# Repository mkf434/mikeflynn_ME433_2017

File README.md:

Name: Mike Flynn
Date: September 2017

This repository has my homework files and anything else I needed to create for ME433: Advanced Mechantronics at Northwestern

Here is another line I'm writing to modify the file on my computer locally to make double sure I know how to commit modifed files

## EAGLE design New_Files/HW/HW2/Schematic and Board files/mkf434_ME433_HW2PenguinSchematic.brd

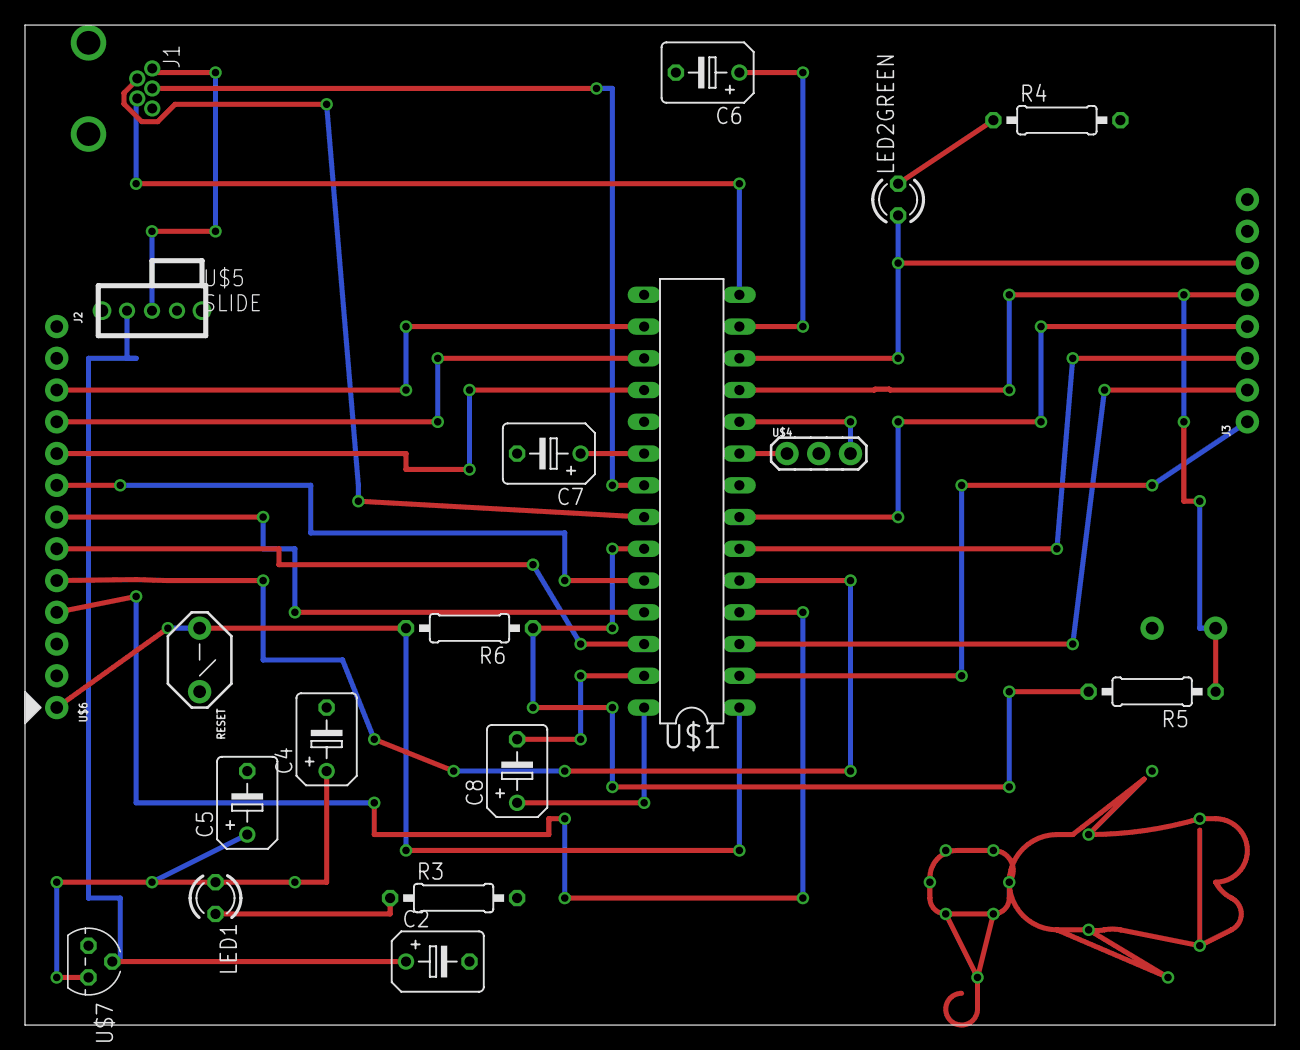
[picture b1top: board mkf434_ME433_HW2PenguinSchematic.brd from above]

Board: 2 copper layers, 100.0 x 80.0 mm, 22 parts (1 on the bottom side), 31 nets.

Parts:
C2, C4, C6, C8: 0.1uF; B45181B
C5, C7: 10uF; B45181B
J1: USB-MB-H
J2, J3: 1X08
LED1, LED2GREEN: LED3MM
R3, R4: 330; 0207/10
R5, R6: 10k; 0207/10
RESET: PB
U$1: PIC32MX250F128B; DIL28-3
U$4: OSC
U$5: SLIDE
U$6: PICKIT3; 1X05
U$7: MCP1702; TO92
USER: PB

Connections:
+3V3: R5.2, R6.1, U$1.23
A0: J3.1, U$1.2
A1: J3.2, U$1.3
A4/LED: J3.6, LED2GREEN.A, U$1.12
B2: J3.3, U$1.6
B3: J3.4, U$1.7
B4/USER: J3.5, R5.1, U$1.11, USER.1
B7: J2.3, U$1.16
B8: J2.4, U$1.17
B9: J2.5, U$1.18
B13: J2.6, U$1.24
B14: J2.7, U$1.25
B15: J2.8, U$1.26
D+: J1.D+, U$1.21
D-: J1.D-, U$1.22
GND: C2.-, C4.-, C5.-, C6.-, C7.-, J1.GND, R3.2, R4.2, RESET.2, U$1.8, U$1.19, U$4.2, U$6.3, U$7.1, USER.2
ID: J1.ID, U$1.14
MCLR: R6.2, RESET.1, U$1.1, U$6.1
unnamed: J1.VBUS, U$5.2.
unnamed: C2.+, U$5.1., U$7.2
unnamed: C4.+, C5.+, LED1.A, U$7.3
unnamed: LED1.K, R3.1
unnamed: LED2GREEN.K, R4.1
unnamed: C6.+, U$1.13
unnamed: C7.+, U$1.20
unnamed: C8.+, U$1.28
unnamed: C8.-, U$1.27
OSC1: U$1.9, U$4.1
OSC2: U$1.10, U$4.3
PGC: U$1.5, U$6.5
PGD: U$1.4, U$6.4

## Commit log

2017-04-03 added readme.md finallygit status
2017-04-03 Forgot to save my file
2017-04-03 Update README.md again
2017-04-05 First Deliverable Photo
2017-04-05 Hw1 Question 6 requested picture
2017-04-07 HW3 ZIP Files
2017-08-24 Second half of homework 1 deliverables
2017-08-24 File Name Updates
2017-09-20 Date Change
2018-04-19 Re-organizing repoallowing for easier identification of New Files
2018-04-27 Cleaned out old files, added new hw files, HW1.2.1 and HW1.2.2
2018-04-27 Deleted more extra files, added Hello World for HW1.7
2018-04-27 Started Hello World file and other asscoiated files
2018-04-27 Saved Hello_World433.c
2018-04-27 Deleted Extra File
2018-04-27 Save File
2018-05-03 Adding hw1 updates
2018-05-03 Random Files from MPlab
2018-05-03 Task1
2018-05-03 HW1 Video
2018-05-03 HW2 fies
2018-05-03 HW3 Files
2018-05-03 Missed HW2 files
2018-05-03 Added some lines I deleted because I thought they were vestigle but I put them back once I realized they were in the template on the wiki
2018-05-07 Start of HW4
2018-05-07 Trying to get rid of an 'Untracked file'
2018-05-07 Added Helper Functions into HW4 main
2018-05-08 Silly Changes
2018-05-08 Saving HW4, got a signal from the MCP4902, trying to manipulate it now
2018-05-08 Stragler File
2018-05-08 Saving HW4
2018-05-08 Almost got SPI, signing off
2018-05-13 Almost done with HW4, finished triangle wave, having casting problems using sin() with doubles butneeding ints for SPI
2018-05-13 Random File
2018-05-13 Homework 4 finished, just need to clean up the code and draw the schematic
2018-05-13 Finished HW4, onto HW5, can't stop wont stop
2018-05-13 Homework 5 is well underway, just put in the I2C functions from github and put in the helper function prototypes mentionedin the instructions
2018-05-13 Added more things, writing init functions and mcp23008 register init functions
2018-05-13 Finished first draft of the code, about to turn it on, potential second first try success ever
2018-05-13 Wrote the main function, seems to easy to be correct
2018-05-13 Had the wrong master_setup values, also had the wrong slave address bits
2018-05-14 Got the MCP23008 to output and have basic right control, now I need to verify that my read is correct
2018-05-14 Finished homework 5, something might be wrong with my GP7, but I got creative with it so we good
2018-05-14 Added video
2018-05-14 Cleaned up the comments on HW5 and added a header comment to HW1
2018-05-14 Stragler Files
2018-05-14 Almost forgot the picture of the circuit
2018-05-14 Rolling right along, created the HW6 folder
2018-05-14 Changed some HW5 stuff, started adding the files needed for the LCD driver
2018-05-14 Changed file and project names to the homework they correspond to and the main files to mainx.c where x is the homework#
2018-05-14 Changed some reference files
2018-05-14 Saving HW6 progress
2018-05-15 Almost finished with the first function
2018-05-15 Finished the writing a character function
2018-05-15 Finished HW6, just adding in the final comments and cleaning everything up etc, signing off for the night
2018-05-15 Finished everything in homework 6
2018-05-15 Created Main file skeleton and started homework 7
2018-05-15 HW7 changes
2018-05-17 Did some directory reorganization, added a LCD and I2C library from past hws
2018-05-17 Hopefully this adds all new files
2018-05-18 Recieved Correct WHO_AM_I response from pololu chip
2018-05-18 Missed some files
2018-05-18 Straglers
2018-05-20 Almost finished with HW7, not sure what the units of the data being sent is, need to ask marchuk
2018-05-20 Adding Stuff
2018-05-20 More
2018-05-21 HW8 done, once I finish off the bugs from HW6 and HW7, HW9 is well underway as well
2018-05-21 Stagler
2018-06-04 Added a lot of stuff
2018-06-04 Wheel
2018-06-04 Hello
2018-06-04 Finished CAD and Laser Files
2018-06-05 Completely finished HW6, resolved issue where chars were writing over each other
2018-06-05 HW6 Video Added
2018-06-05 Finished HW8, just need to finish HW7 accel bars
2018-06-05 Restarted HW9 and almost back to where I was, didn't work the first time so I regenerated the code to make sure I set everything up correctly
2018-06-05 Stragler
2018-06-05 Had to change New Files to New_Files bc of Andriod Developer IDE
2018-06-05 Changed 'Old Files' also for continuity
2018-06-05 Cleaning House
2018-06-05 Still cleaning, hopefully I don't delete everything
2018-06-05 Started Andriod Hello World
2018-06-06 Almost done with Android Hello World App
2018-06-06 Finished HW 12
2018-06-06 Added HW12 Demo Video
2018-06-09 Added Photo of current wiring
2018-06-09 Added first version of living hinge
2018-06-09 Edited HW12 and HW13
2018-06-09 Added HW18 Code
2018-06-09 Added V2 Wheels with correctly fitting o rings
2018-06-10 Started Final PCB Solder
